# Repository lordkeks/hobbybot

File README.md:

# hobbybot
 Small differential drive platform for robotics projects

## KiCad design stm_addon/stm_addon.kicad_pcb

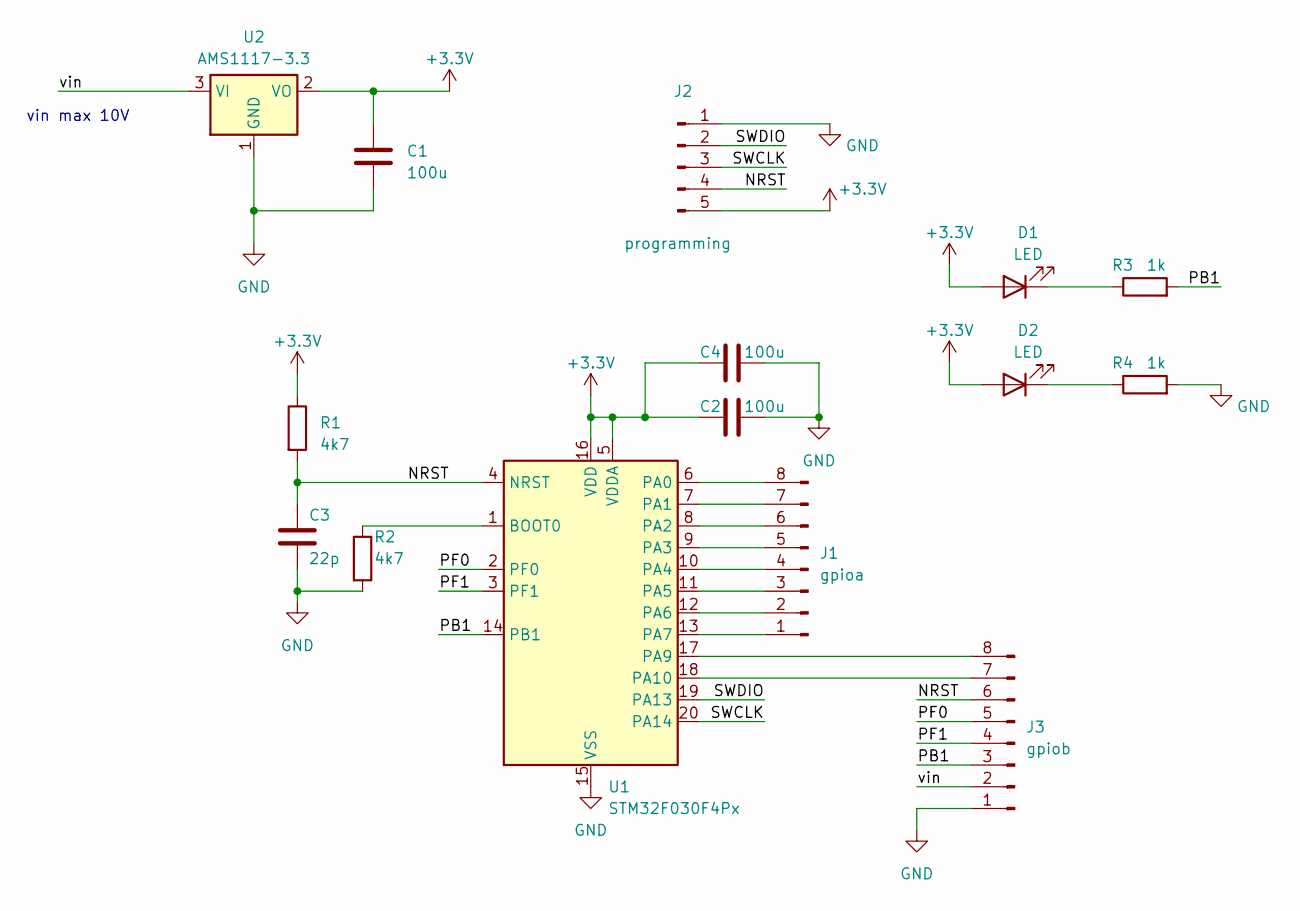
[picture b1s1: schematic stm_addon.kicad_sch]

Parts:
C1, C2, C4: 100u; C_0402_1005Metric
C3: 22p; C_0402_1005Metric
D1, D2: LED; LED_0603_1608Metric; mpn 0603GBD0790S01
J1: gpioa; PinHeader_1x08_P2.54mm_Vertical
J2: programming; PinHeader_1x05_P2.54mm_Vertical
J3: gpiob; PinHeader_1x08_P2.54mm_Vertical
R1, R2: 4k7; R_0402_1005Metric
R3, R4: 1k; R_0402_1005Metric
U1: STM32F030F4Px; TSSOP-20_4.4x6.5mm_P0.65mm; mpn STM32F030F4P6TR
U2: AMS1117-3.3; SOT-223-3_TabPin2; mpn AMS1117-3.3

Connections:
+3.3V: C1.1, C2.1, C4.1, D1.2 (A), D2.2 (A), J2.5, R1.1, U1.5 (VDDA), U1.16 (VDD), U2.2 (VO)
/NRST: C3.1, J2.4, J3.6, R1.2, U1.4 (NRST)
/PB1: J3.3, R3.2, U1.14 (PB1)
/PF0: J3.5, U1.2 (PF0)
/PF1: J3.4, U1.3 (PF1)
/SWCLK: J2.3, U1.20 (PA14)
/SWDIO: J2.2, U1.19 (PA13)
/vin: J3.2, U2.3 (VI)
GND: C1.2, C2.2, C3.2, C4.2, J2.1, J3.1, R2.2, R4.2, U1.15 (VSS), U2.1 (GND)
unnamed: D1.1 (K), R3.1
unnamed: D2.1 (K), R4.1
unnamed: J1.1, U1.13 (PA7)
unnamed: J1.2, U1.12 (PA6)
unnamed: J1.3, U1.11 (PA5)
unnamed: J1.4, U1.10 (PA4)
unnamed: J1.5, U1.9 (PA3)
unnamed: J1.6, U1.8 (PA2)
unnamed: J1.7, U1.7 (PA1)
unnamed: J1.8, U1.6 (PA0)
unnamed: J3.7, U1.18 (PA10)
unnamed: J3.8, U1.17 (PA9)
unnamed: R2.1, U1.1 (BOOT0)

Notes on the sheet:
vin max 10V

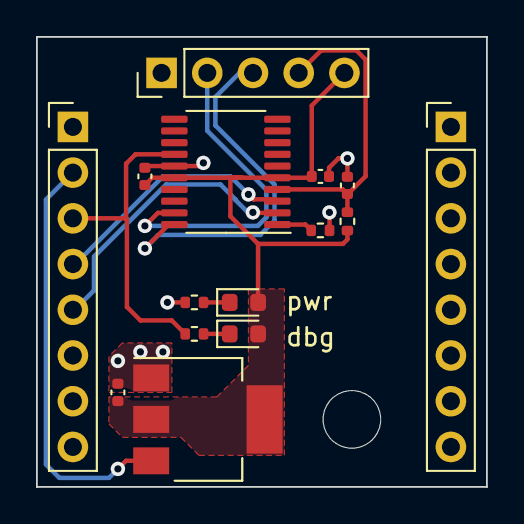
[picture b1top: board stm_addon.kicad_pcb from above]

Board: 2 copper layers, 25.0 x 25.0 mm, 15 parts (0 on the bottom side), 22 nets.

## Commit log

2023-09-19 update baseplate
2023-09-19 added piplate
2023-09-19 rename mech folder
